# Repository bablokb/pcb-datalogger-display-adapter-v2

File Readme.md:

KiCAD-Designfiles
=================

Here are the KiCAD (v7) design-files for a generic display-adapter-PCB.

The adapter supports the following displays:

  - Pimoroni Inky-Pack (and other display-packs with the same pinout)
  - Adafruit SPI-displays
  - WeAct-Studio 2.9" B/W e-Ink (with 2x4 connector)
  - Various generic SPI-TFT displays (many share the same pinout)

The pinout of the "input pins" is optimized for these datalogger PCB:

  - [Datalogger-v2 PCB](https://github.com/bablokb/pcb-datalogger-v2)
  - [Datalogger-v3 PCB](https://github.com/bablokb/pcb-datalogger-v3)

There is a minimal case available for the display, mainly to stabilze it:

Schematic
---------

Layout
------

3D-Views
--------

License
-------

[![CC BY-SA 4.0][cc-by-sa-shield]][cc-by-sa]

This work is licensed under a
[Creative Commons Attribution-ShareAlike 4.0 International
License][cc-by-sa].

[![CC BY-SA 4.0][cc-by-sa-image]][cc-by-sa]

[cc-by-sa]: http://creativecommons.org/licenses/by-sa/4.0/
[cc-by-sa-image]: https://licensebuttons.net/l/by-sa/4.0/88x31.png
[cc-by-sa-shield]:
https://img.shields.io/badge/License-CC%20BY--SA%204.0-lightgrey.svg

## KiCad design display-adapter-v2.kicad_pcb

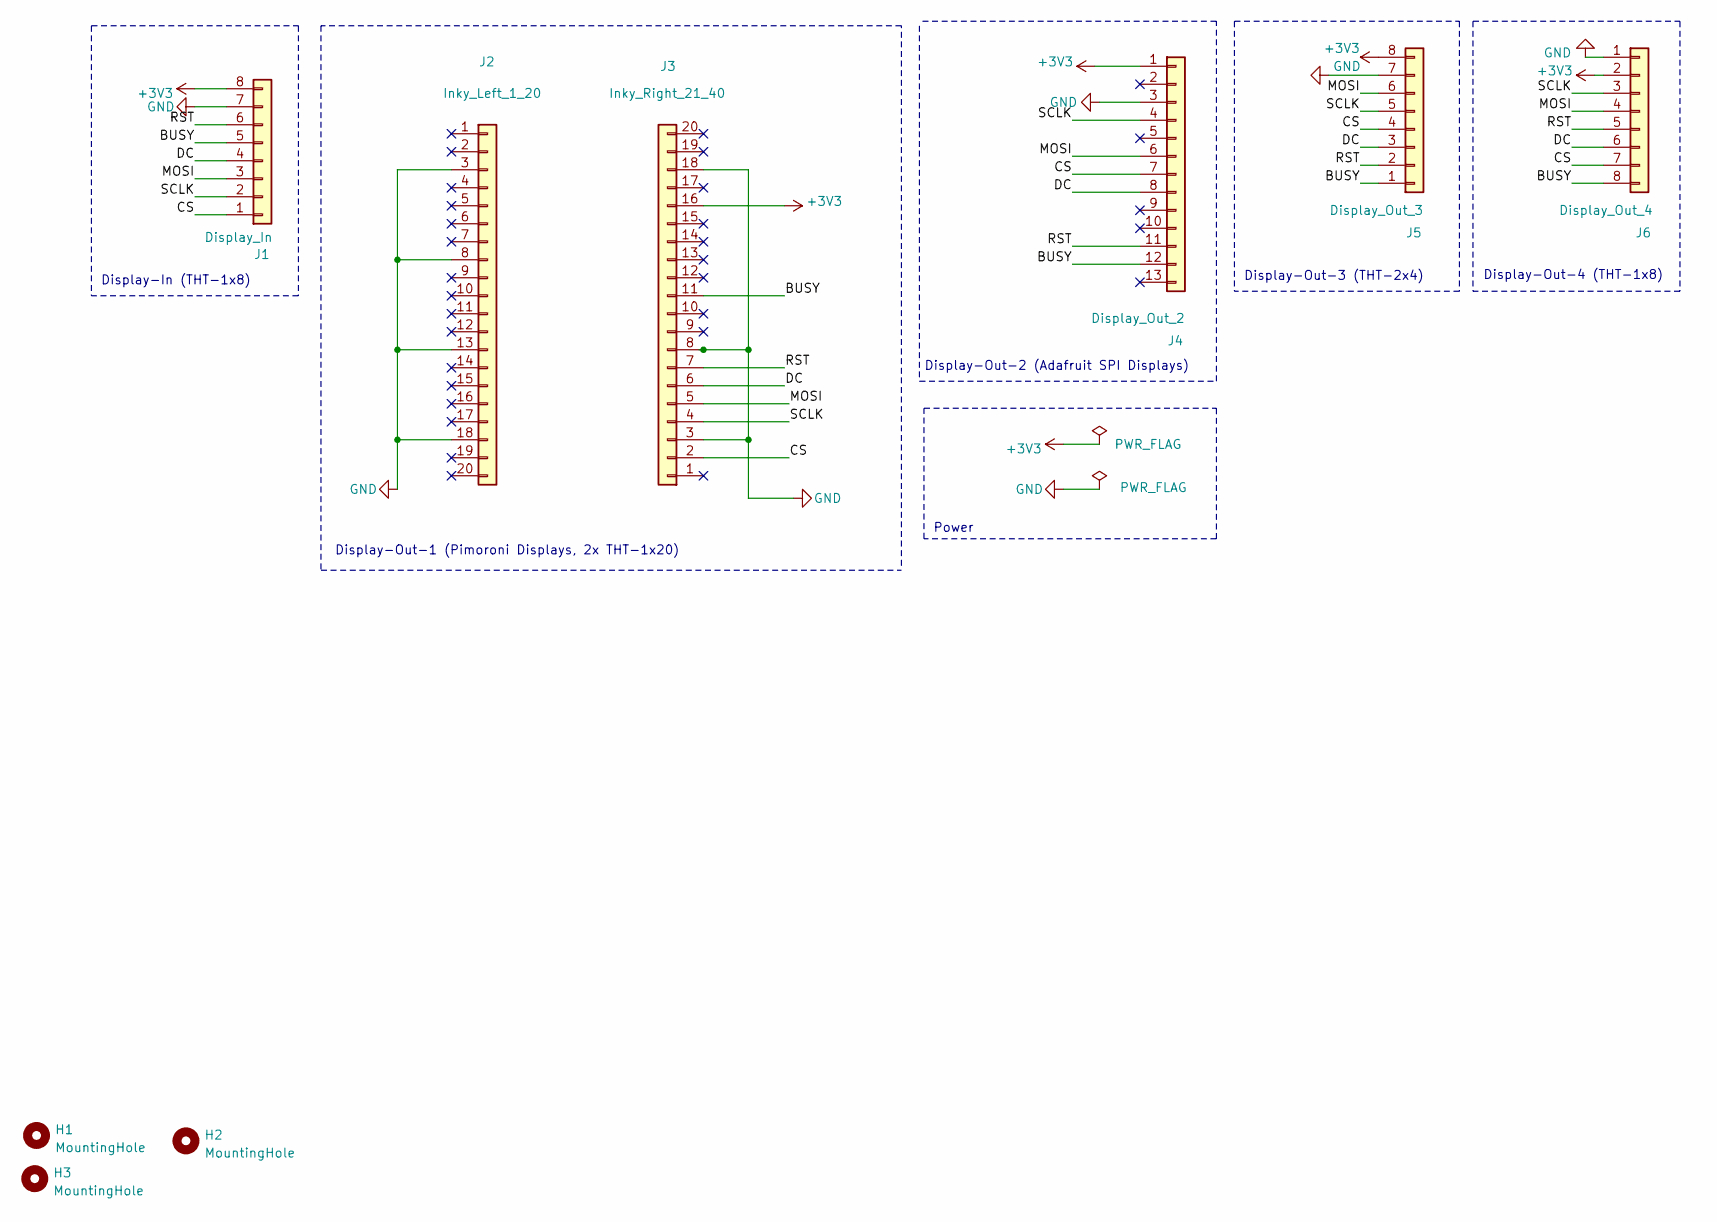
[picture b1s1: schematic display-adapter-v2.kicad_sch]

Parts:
H1, H2, H3: MountingHole; MountingHole_2.5mm
J1: Display_In; PinHeader_1x08_P2.54mm_Vertical; LCSC C5143489
J2: Inky_Left_1_20; PinHeader_1x20_P2.54mm_Vertical; LCSC C725952
J3: Inky_Right_21_40; PinHeader_1x20_P2.54mm_Vertical; LCSC C725952
J4: Display_Out_2; PinSocket_1x13_P2.54mm_Vertical
J5: Display_Out_3; PinSocket_2x04_P2.54mm_Vertical
J6: Display_Out_4; PinSocket_1x08_P2.54mm_Vertical; LCSC C5143489

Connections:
+3V3: J1.8, J3.16, J4.1, J5.8, J6.2
/BUSY: J1.5, J3.11, J4.12, J5.1, J6.8
/CS: J1.1, J3.2, J4.7, J5.4, J6.7
/DC: J1.4, J3.6, J4.8, J5.3, J6.6
/MOSI: J1.3, J3.5, J4.6, J5.6, J6.4
/RST: J1.6, J3.7, J4.11, J5.2, J6.5
/SCLK: J1.2, J3.4, J4.4, J5.5, J6.3
GND: J1.7, J2.3, J2.8, J2.13, J2.18, J3.3, J3.8, J3.18, J4.3, J5.7, J6.1

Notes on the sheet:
Display-Out-1 (Pimoroni Displays, 2x THT-1x20)
Display-Out-3 (THT-2x4)
Display-Out-2 (Adafruit SPI Displays)
Display-Out-4 (THT-1x8)
Power
Display-In (THT-1x8)

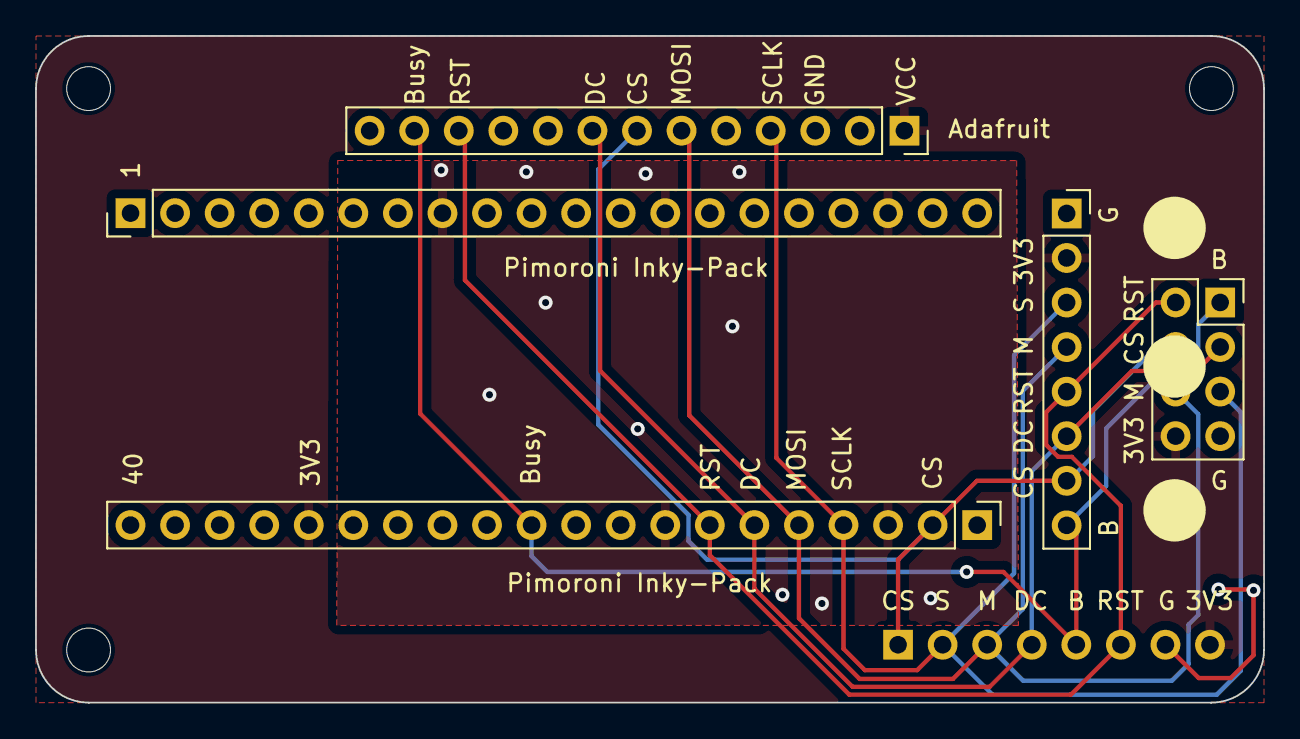
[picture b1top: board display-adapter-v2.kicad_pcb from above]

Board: 2 copper layers, 70.0 x 38.0 mm, 9 parts (1 on the bottom side), 8 nets.

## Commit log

2026-02-23 initial commit (Rev. 1.00)
2026-03-12 bugfix: wrong 1x21 instead of 1x20 footprint for Inky-connectors
2026-04-08 added submodule
2026-04-08 removed .gitmodules
2026-04-08 ignore 3D print files
2026-04-08 updated to newest version of modules
2026-04-08 initial version of case for display-adapter
2026-04-10 also exclude *.bgcode
2026-04-14 added images of case
2026-04-14 removed doubled links
